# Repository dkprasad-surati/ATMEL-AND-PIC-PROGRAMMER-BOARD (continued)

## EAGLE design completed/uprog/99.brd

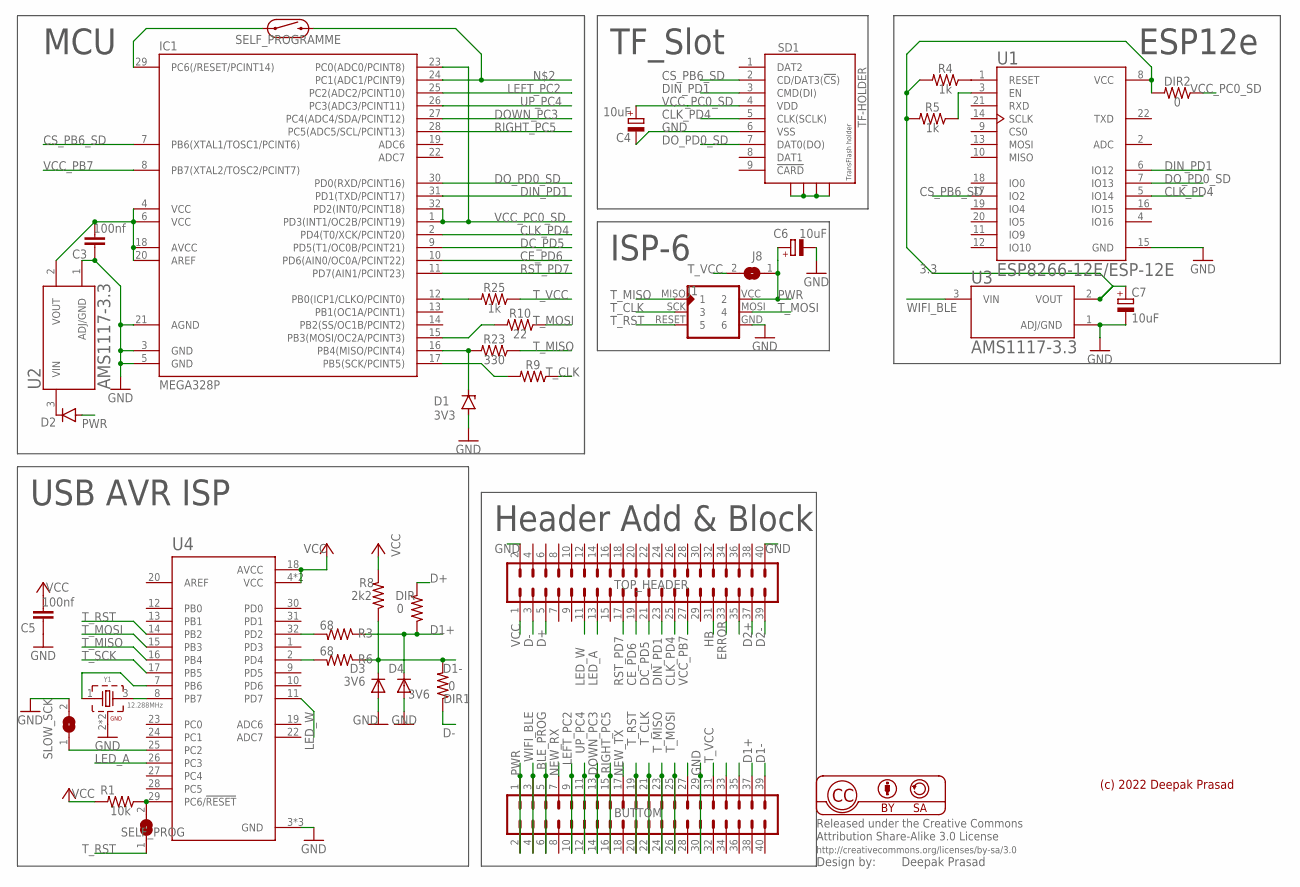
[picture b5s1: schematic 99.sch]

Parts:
BUTTOM: MA20-2
C3, C5: 100nf; C1206
C4, C6, C7: 10uF; C/6032-28R
D1: 3V3; SOD80C
D2: DIODE-DO214AC; DO214AC
D3, D4: 3V6; SMA-DIODE
DIR, DIR1, DIR2: 0; RESC3216X70
IC1: MEGA328P; TQFP32-08
J1: AVR-ISP-6PINAVR-ISP-6PIN; AVR-ISP-6PIN
J8: SJW
R1: 10k; RESC3216X70
R3, R6: 68; RESC3216X70
R4, R5, R25: 1k; RESC3216X70
R8: 2k2; RESC3216X70
R9, R10: 22; RESC3216X70
R23: 330; RESC3216X70
SD1: TF-HOLDER; TF-PULL
SELF_PROG: SJW
SELF_PROGRAMME: REED_SWITCH-PTH-GLASS; REED_SWITCH_GLASS
SLOW_SCK: SJW
TOP_HEADER: MA20-2
U1: ESP8266-12E/ESP-12E; XCVR_ESP8266-12E/ESP-12E
U2, U3: AMS1117-3.3; SOT229P700X180-4N
U4: ATMEGA328P-AU; QFP80P900X900X120-32N
Y1: 12.288MHz; WE-XTAL_CFPX-104

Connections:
3.3: C7.+, DIR2.2, R4.2, R5.2, U1.8 (VCC), U3.2 (VOUT)
BLE_PROG: BUTTOM.5, BUTTOM.6
CE_PD6: IC1.10 (PD6(AIN0/OC0A/PCINT22)), TOP_HEADER.19
CLK_PD4: IC1.2 (PD4(T0/XCK/PCINT20)), SD1.5 (CLK(SCLK)), TOP_HEADER.25, U1.5 (IO14)
CS_PB6_SD: IC1.7 (PB6(XTAL1/TOSC1/PCINT6)), SD1.2 (CD/DAT3(!CS!)), U1.17 (IO2)
D1+: BUTTOM.37, D4.C, DIR.1, R3.1
D1-: BUTTOM.39, D3.C, DIR1.2, R6.1, R8.1
D2+: TOP_HEADER.37
D2-: TOP_HEADER.39
D+: DIR.2, TOP_HEADER.5
D-: DIR1.1, TOP_HEADER.3
DC_PD5: IC1.9 (PD5(T1/OC0B/PCINT21)), TOP_HEADER.21
DIN_PD1: IC1.31 (PD1(TXD/PCINT17)), SD1.3 (CMD(DI)), TOP_HEADER.23, U1.6 (IO12)
DOWN_PC3: BUTTOM.13, BUTTOM.14, IC1.27 (PC4(ADC4/SDA/PCINT12))
DO_PD0_SD: IC1.30 (PD0(RXD/PCINT16)), SD1.7 (DAT0(DO)), U1.7 (IO13)
ERROR: TOP_HEADER.33
GND: BUTTOM.29, BUTTOM.30, C3.1, C4.-, C5.1, C6.-, C7.-, D1.A, D3.A, D4.A, IC1.3 (GND), IC1.5 (GND), IC1.21 (AGND), J1.GND (6), SD1.6 (VSS), SLOW_SCK.2, TOP_HEADER.2, TOP_HEADER.40, U1.15 (GND), U2.1 (ADJ/GND), U3.1 (ADJ/GND), U4.3 (GND), U4.5 (GND), U4.21 (GND), Y1.2 (GND), Y1.4 (GND)
GND1: SD1.S1, SD1.S2, SD1.S3, SD1.S4
HB: TOP_HEADER.31
LED_A: TOP_HEADER.13, U4.26 (PC3)
LED_W: TOP_HEADER.11, U4.11 (PD7)
LEFT_PC2: BUTTOM.9, BUTTOM.10, IC1.25 (PC2(ADC2/PCINT10))
unnamed: U4.8 (PB7), Y1.3 (2)
unnamed: IC1.24 (PC1(ADC1/PCINT9)), SELF_PROGRAMME.P$2 (2)
unnamed: R4.1, U1.1 (RESET)
unnamed: R5.1, U1.3 (EN)
unnamed: IC1.12 (PB0(ICP1/CLKO/PCINT0)), R25.2
unnamed: D1.C, IC1.16 (PB4(MISO/PCINT4)), R23.2
unnamed: U4.7 (PB6), Y1.1
unnamed: C3.2, IC1.4 (VCC), IC1.6 (VCC), IC1.18 (AVCC), IC1.20 (AREF), U2.2 (VOUT)
unnamed: R1.1, SELF_PROG.2, U4.29 (PC6/!RESET)
unnamed: D2.C, U2.3 (VIN)
unnamed: IC1.29 (PC6(/RESET/PCINT14)), SELF_PROGRAMME.P$1 (1)
unnamed: SLOW_SCK.1, U4.25 (PC2)
unnamed: R3.2, U4.32 (PD2)
unnamed: R6.2, U4.2 (PD4)
unnamed: IC1.15 (PB3(MOSI/OC2A/PCINT3)), R10.2
unnamed: IC1.17 (PB5(SCK/PCINT5)), R9.2
NEW_RX: BUTTOM.7
NEW_TX: BUTTOM.17
PWR: BUTTOM.1, BUTTOM.2, C6.+, D2.A, J1.VCC (2), J8.1
RIGHT_PC5: BUTTOM.15, BUTTOM.16, IC1.28 (PC5(ADC5/SCL/PCINT13))
RST_PD7: IC1.11 (PD7(AIN1/PCINT23)), TOP_HEADER.17
T_CLK: BUTTOM.21, BUTTOM.22, J1.SCK (3), R9.1
T_MISO: BUTTOM.23, BUTTOM.24, J1.MISO (1), R23.1, U4.16 (PB4)
T_MOSI: BUTTOM.25, BUTTOM.26, J1.MOSI (4), R10.1, U4.15 (PB3)
T_RST: BUTTOM.19, BUTTOM.20, J1.RESET (5), SELF_PROG.1, U4.14 (PB2)
T_SCK: U4.17 (PB5)
T_VCC: BUTTOM.31, J8.2, R25.1
UP_PC4: BUTTOM.11, BUTTOM.12, IC1.26 (PC3(ADC3/PCINT11))
VCC: C5.2, R1.2, R8.2, TOP_HEADER.1, U4.4 (VCC), U4.6 (VCC), U4.18 (AVCC)
VCC_PB7: IC1.8 (PB7(XTAL2/TOSC2/PCINT7)), TOP_HEADER.27
VCC_PC0_SD: C4.+, DIR2.1, IC1.1 (PD3(INT1/OC2B/PCINT19)), IC1.23 (PC0(ADC0/PCINT8)), IC1.32 (PD2(INT0/PCINT18)), SD1.4 (VDD)
WIFI_BLE: BUTTOM.3, BUTTOM.4, U3.3 (VIN)

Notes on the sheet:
(c) 2022 Deepak Prasad
Header Add & Block
MCU
TF_Slot
ESP12e
ISP-6
USB AVR ISP

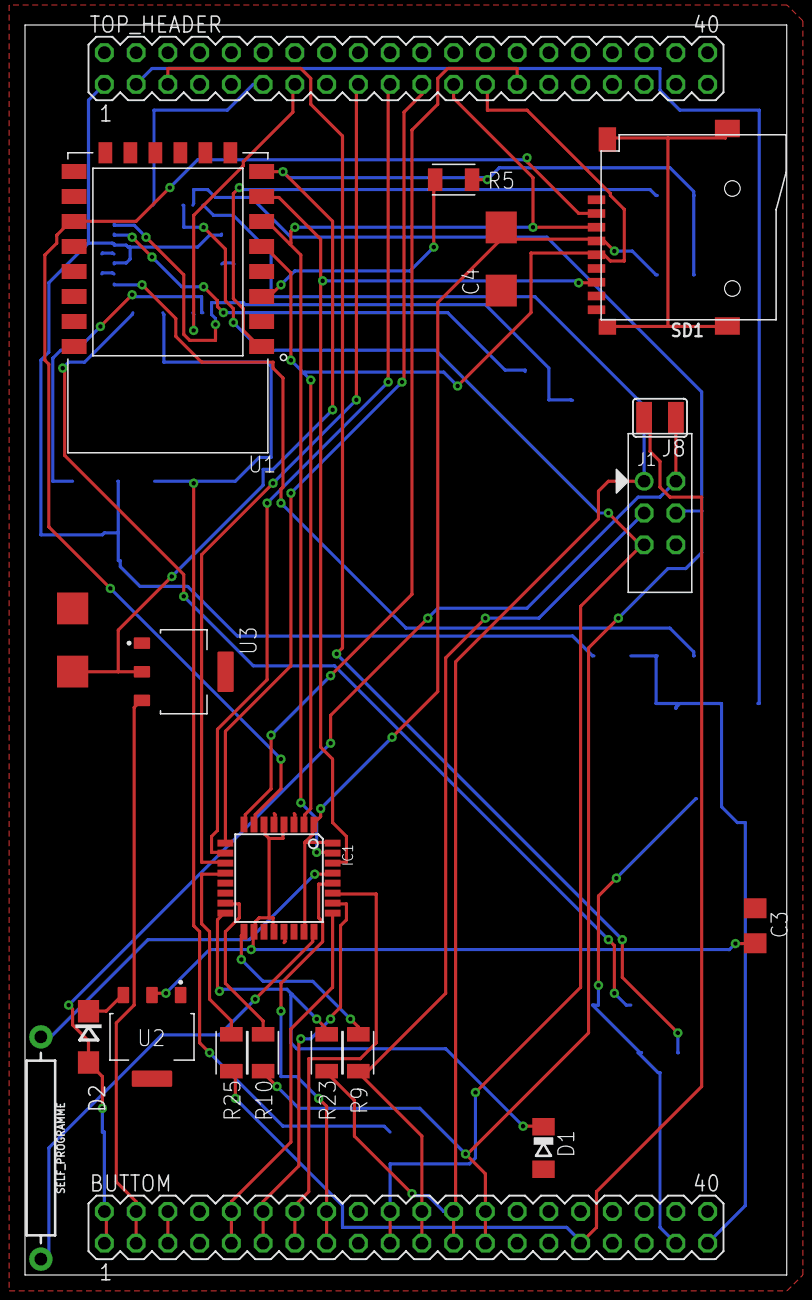
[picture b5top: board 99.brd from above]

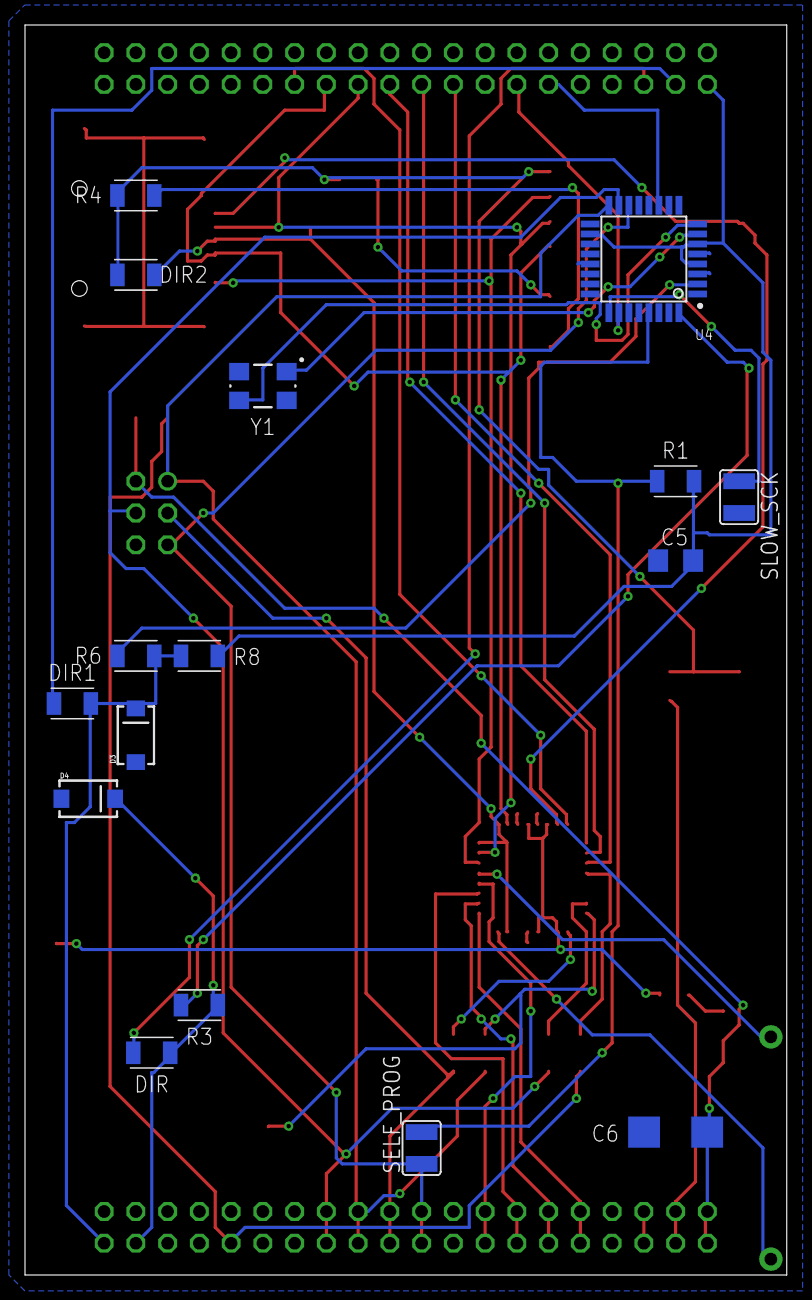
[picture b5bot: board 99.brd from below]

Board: 2 copper layers, 60.9 x 100.0 mm, 36 parts (16 on the bottom side), 47 nets.

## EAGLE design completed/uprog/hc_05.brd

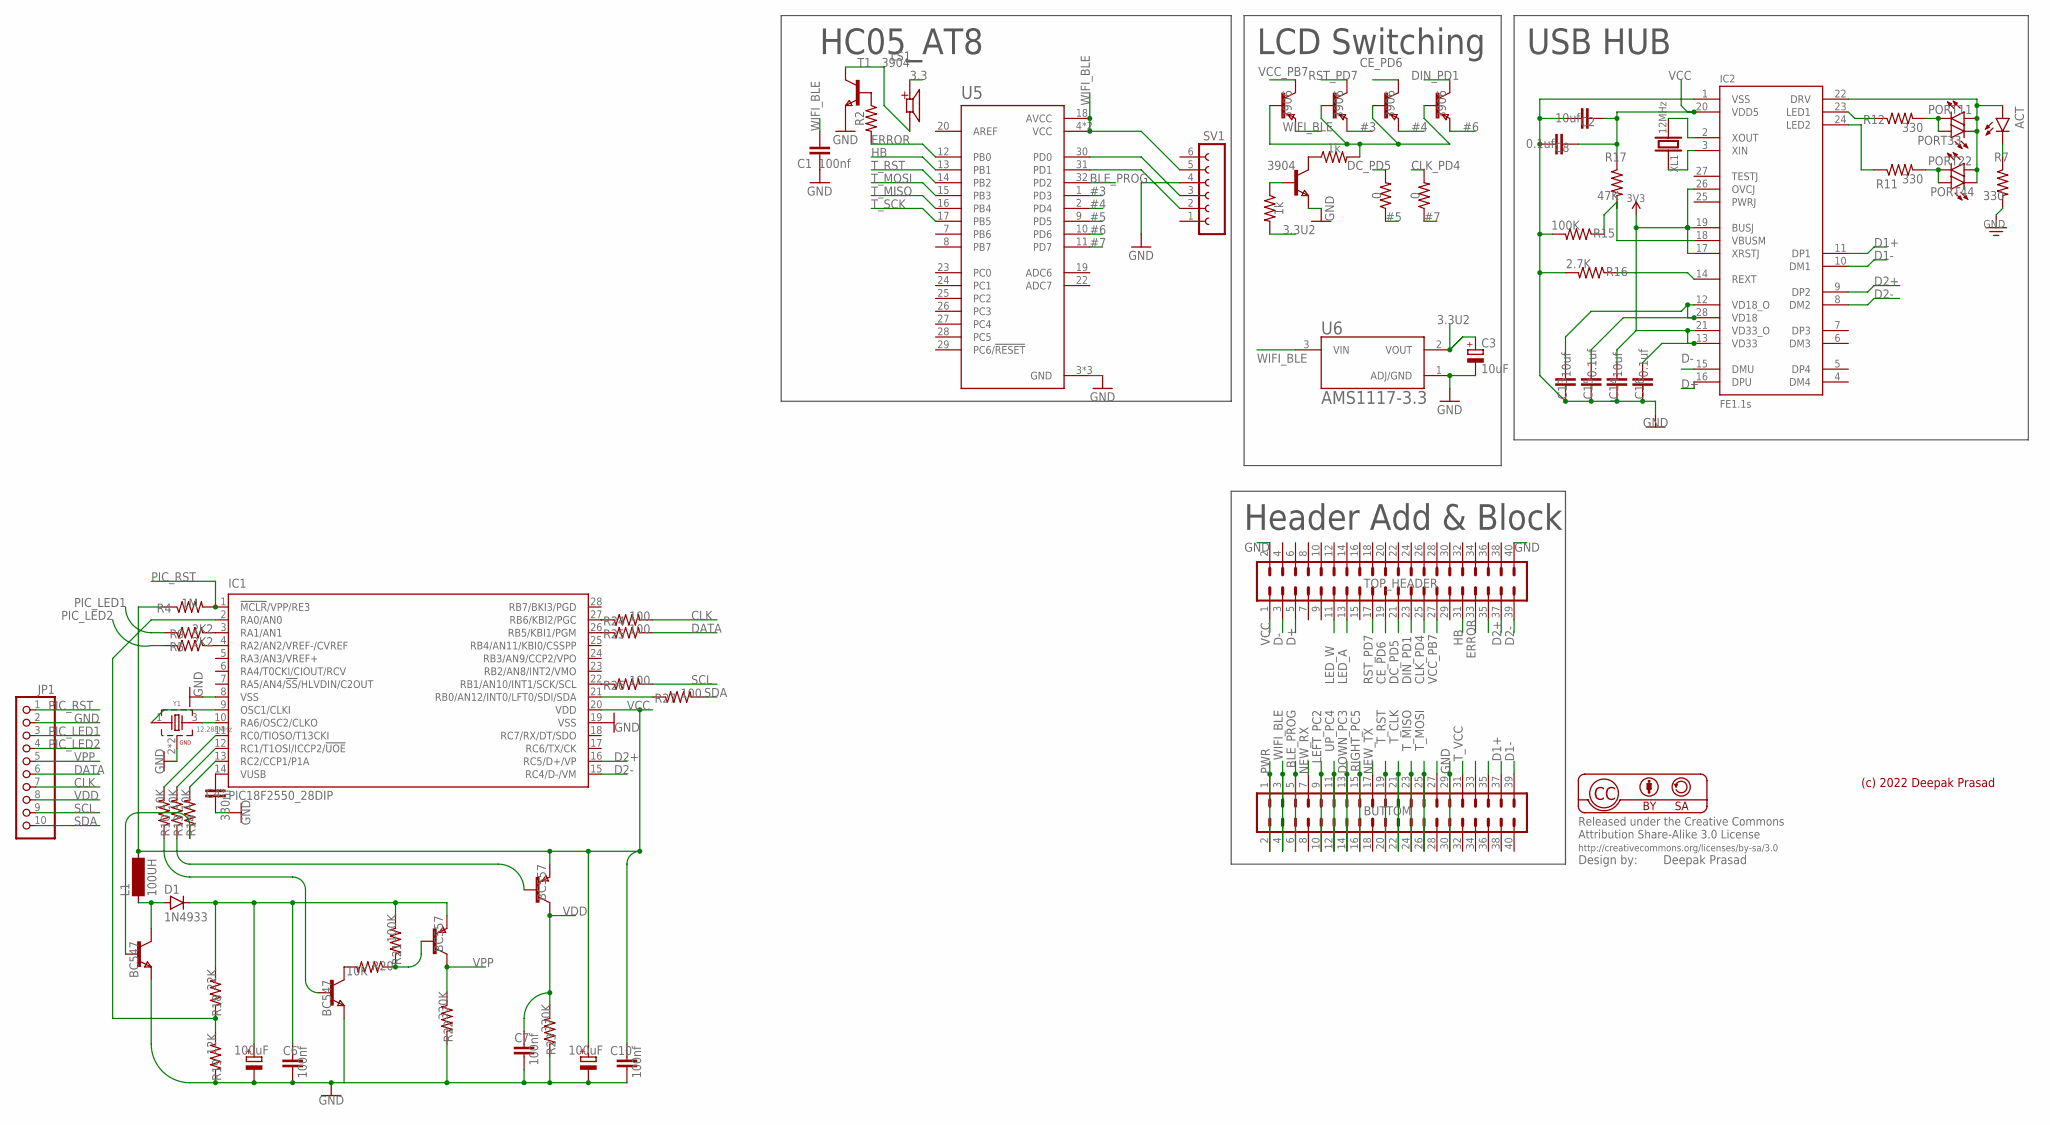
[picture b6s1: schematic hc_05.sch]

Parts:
ACT: LED1206; LED-1206
BUTTOM: MA20-2
C1, C6, C7, C10: 100nf; C1206
C2, C13, C14: 10uf; C1206
C3: 10uF; C/6032-28R
C4: 330nf; C1206
C5, C9: 100uF; C/6032-28R
C8, C15, C16: 0.1uf; C1206
D1: 1N4933; SMB
IC1: PIC18F2550_28DIP; DIL28-3
IC2: FE1.1S; FE1.1S_SSOP-28
JP1: PINHD-1X10; 1X10
L1: 100UH; MS85
LS1: CMT-8530S-SMT; CUI_CMT-8530S-SMT
PORT11, PORT22, PORT33, PORT44: LED1206; LED-1206
R1, R6: 1k; RESC3216X70
R2: 22; RESC3216X70
R3, R8: 0; RESC3216X70
R4: 1M; RESC3216X70
R5, R9: 2K2; RESC3216X70
R7, R11, R12: 330; RESC3216X70
R10, R13, R14, R20: 10K; RESC3216X70
R15, R21: 100K; RESC3216X70
R16: 2.7K; RESC3216X70
R17: 47K; RESC3216X70
R18: 22K; RESC3216X70
R19: 12K; RESC3216X70
R22, R23: 330K; RESC3216X70
R24, R25, R26, R27: 100; RESC3216X70
SV1: FE06-1; FE06
T1, T2: 3904; SOT-23
T3, T4, T5, T6: 3906; SOT-23
T7, T9: BC547; SOT-23
T8, T10: BC557; SOT-23
TOP_HEADER: MA20-2
U5: ATMEGA328P-AU; QFP80P900X900X120-32N
U6: AMS1117-3.3; SOT229P700X180-4N
XL1: 12MHz; HC49UP
Y1: 12.288MHz; WE-XTAL_CFPX-104

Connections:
3.3: LS1.P
3.3U2: C3.+, R6.2, U6.2 (VOUT)
3V3: C14.2, C16.2, IC2.13 (VD33), IC2.17 (XRSTJ), IC2.19 (BUSJ), IC2.21 (VD33_O), IC2.26 (OVCJ)
#3: T4.2 (E), U5.1 (PD3)
#4: T5.2 (E), U5.2 (PD4)
#5: R8.1, U5.9 (PD5)
#6: T6.2 (E), U5.10 (PD6)
#7: R3.1, U5.11 (PD7)
BLE_PROG: BUTTOM.5, BUTTOM.6, U5.32 (PD2)
CE_PD6: T5.1 (C), TOP_HEADER.19
CLK: JP1.7, R24.2
CLK_PD4: R3.2, TOP_HEADER.25
D1+: BUTTOM.37, IC2.11 (DP1)
D1-: BUTTOM.39, IC2.10 (DM1)
D2+: IC1.16 (RC5/D+/VP), IC2.9 (DP2), TOP_HEADER.37
D2-: IC1.15 (RC4/D-/VM), IC2.8 (DM2), TOP_HEADER.39
D+: IC2.16 (DPU), TOP_HEADER.5
D-: IC2.15 (DMU), TOP_HEADER.3
DATA: JP1.6, R25.2
DC_PD5: R8.2, TOP_HEADER.21
DIN_PD1: T6.1 (C), TOP_HEADER.23
DOWN_PC3: BUTTOM.13, BUTTOM.14
ERROR: R2.2, TOP_HEADER.33, U5.12 (PB0)
GND: BUTTOM.29, BUTTOM.30, C1.1, C2.2, C3.-, C4.1, C5.-, C6.1, C7.1, C8.2, C9.-, C10.1, C13.1, C14.1, C15.1, C16.1, IC1.8 (VSS), IC1.19 (VSS), IC2.1 (VSS), JP1.2, R7.2, R15.2, R16.2, R19.1, R22.1, R23.1, SV1.4, T1.2 (E), T2.2 (E), T7.2 (E), T9.2 (E), TOP_HEADER.2, TOP_HEADER.40, U5.3 (GND), U5.5 (GND), U5.21 (GND), U6.1 (ADJ/GND), Y1.2 (GND), Y1.4 (GND)
HB: TOP_HEADER.31, U5.13 (PB1)
LED_A: TOP_HEADER.13
LED_W: TOP_HEADER.11
LEFT_PC2: BUTTOM.9, BUTTOM.10
unnamed: R1.1, T2.1 (C)
unnamed: R1.2, T3.3 (B), T4.3 (B), T5.3 (B), T6.3 (B)
unnamed: IC1.27 (RB6/KBI2/PGC), R24.1
unnamed: R2.1, T1.3 (B)
unnamed: IC1.4 (RA2/AN2/VREF-/CVREF), R5.2
unnamed: IC1.3 (RA1/AN1), R9.2
unnamed: IC1.9 (OSC1/CLKI), Y1.1
unnamed: IC1.10 (RA6/OSC2/CLKO), Y1.3 (2)
unnamed: IC1.11 (RC0/TIOSO/T13CKI), R10.2
unnamed: IC1.12 (RC1/T1OSI/ICCP2/!UOE), R13.2
unnamed: IC1.13 (RC2/CCP1/P1A), R14.2
unnamed: C4.2, IC1.14 (VUSB)
unnamed: R10.1, T9.3 (B)
unnamed: SV1.2, U5.31 (PD1)
unnamed: SV1.3, U5.30 (PD0)
unnamed: R6.1, T2.3 (B)
unnamed: IC2.14 (REXT), R16.1
unnamed: ACT.C, R7.1
unnamed: D1.2 (A), L1.1, T7.1 (C)
unnamed: C13.2, C15.2, IC2.12 (VD18_O), IC2.28 (VD18)
unnamed: C5.+, C6.2, D1.1 (C), R18.2, R21.2, T10.2 (E)
unnamed: R14.1, T7.3 (B)
unnamed: LS1.N, T1.1 (C)
unnamed: IC2.23 (LED1), R12.1
unnamed: IC2.2 (XOUT), XL1.2
unnamed: IC2.3 (XIN), XL1.1
unnamed: PORT11.C, PORT33.A, R12.2
unnamed: PORT22.C, PORT44.A, R11.2
unnamed: IC1.2 (RA0/AN0), R18.1, R19.2
unnamed: R13.1, T8.3 (B)
unnamed: R20.2, T9.1 (C)
unnamed: R20.1, R21.1, T10.3 (B)
unnamed: IC1.26 (RB5/KBI1/PGM), R25.1
unnamed: IC1.22 (RB1/AN10/INT1/SCK/SCL), R26.1
unnamed: IC1.21 (RB0/AN12/INT0/LFT0/SDI/SDA), R27.1
unnamed: IC2.18 (VBUSM), R15.1, R17.2
unnamed: IC2.24 (LED2), R11.1
unnamed: ACT.A, IC2.22 (DRV), PORT11.A, PORT22.A, PORT33.C, PORT44.C
NEW_RX: BUTTOM.7
NEW_TX: BUTTOM.17
PIC_LED1: JP1.3, R9.1
PIC_LED2: JP1.4, R5.1
PIC_RST: IC1.1 (!MCLR!/VPP/RE3), JP1.1, R4.2
PWR: BUTTOM.1, BUTTOM.2
RIGHT_PC5: BUTTOM.15, BUTTOM.16
RST_PD7: T4.1 (C), TOP_HEADER.17
SCL: JP1.9, R26.2
SDA: JP1.10, R27.2
T_CLK: BUTTOM.21, BUTTOM.22
T_MISO: BUTTOM.23, BUTTOM.24, U5.16 (PB4)
T_MOSI: BUTTOM.25, BUTTOM.26, U5.15 (PB3)
T_RST: BUTTOM.19, BUTTOM.20, U5.14 (PB2)
T_SCK: U5.17 (PB5)
T_VCC: BUTTOM.31
UP_PC4: BUTTOM.11, BUTTOM.12
VCC: C2.1, C8.1, C9.+, C10.2, IC1.20 (VDD), IC2.20 (VDD5), L1.2, R4.1, R17.1, T8.2 (E), TOP_HEADER.1
VCC_PB7: T3.1 (C), TOP_HEADER.27
VDD: C7.2, JP1.8, R23.2, T8.1 (C)
VPP: JP1.5, R22.2, T10.1 (C)
WIFI_BLE: BUTTOM.3, BUTTOM.4, C1.2, SV1.5, T3.2 (E), U5.4 (VCC), U5.6 (VCC), U5.18 (AVCC), U6.3 (VIN)

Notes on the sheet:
(c) 2022 Deepak Prasad
Header Add & Block
HC05_AT8
USB HUB
LCD Switching

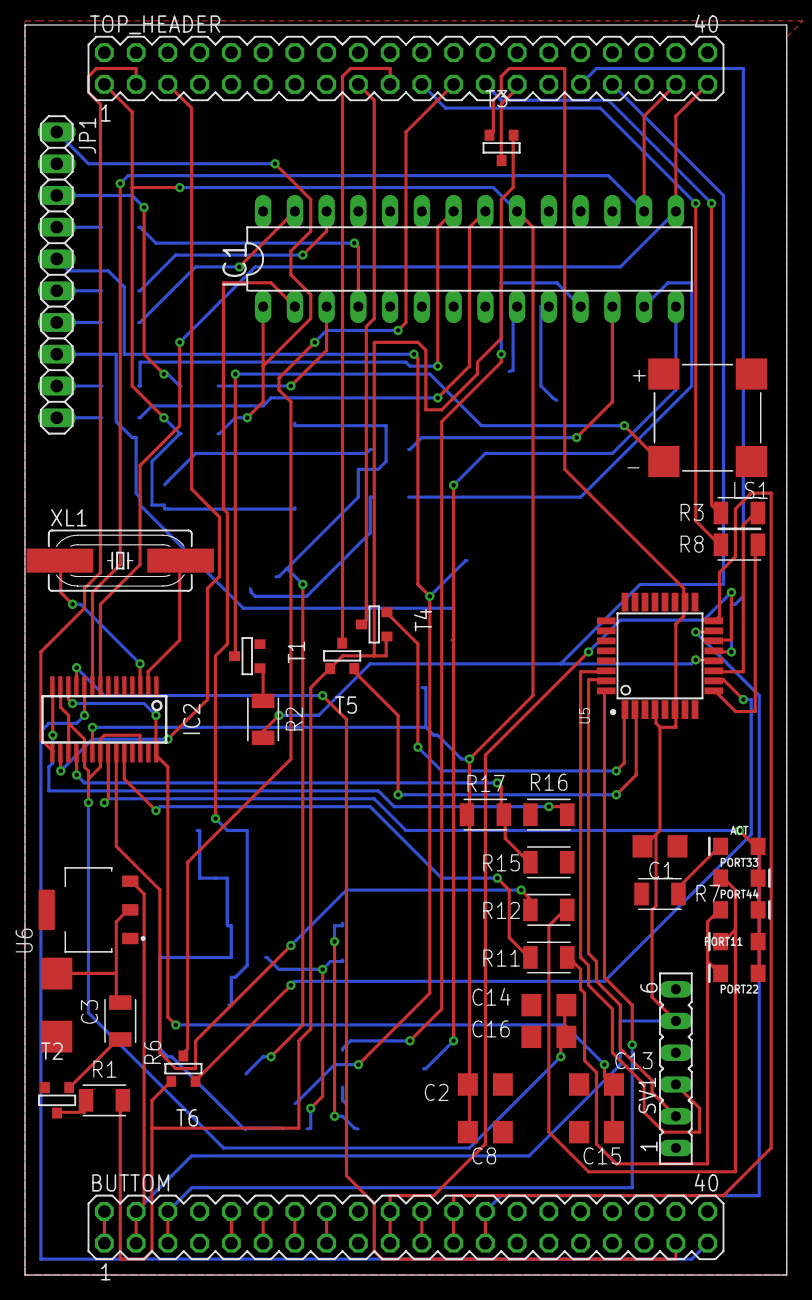
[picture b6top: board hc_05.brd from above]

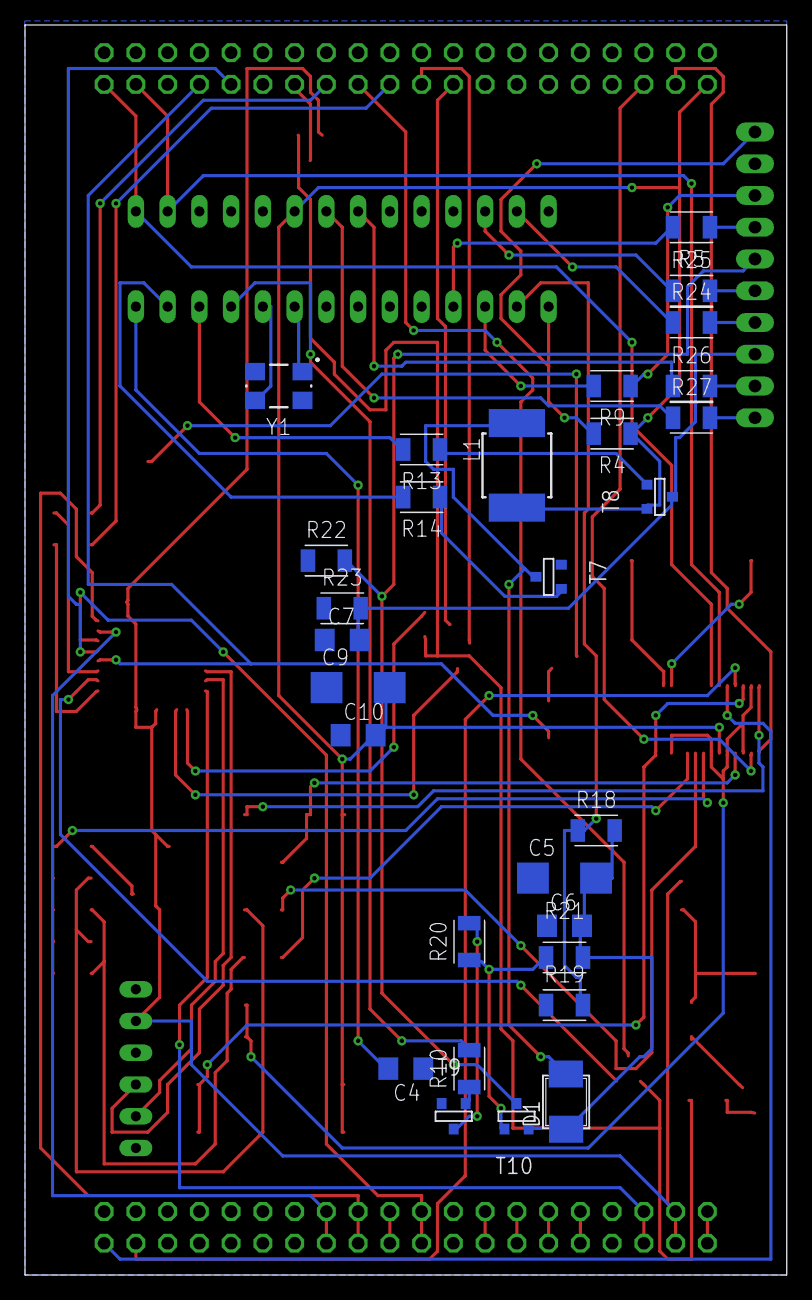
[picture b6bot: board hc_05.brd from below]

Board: 2 copper layers, 60.9 x 100.0 mm, 69 parts (29 on the bottom side), 81 nets.

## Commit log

2023-10-29 FILES
